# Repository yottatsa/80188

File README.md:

# 80188 single board modular computer

* testing and firmware development: r1
* hardware development: r2
  - [CPU card](https://github.com/yottatsa/80188/blob/main/cpu_card/cpu_card/cpu_card.pdf)
  - [ISP interface](https://github.com/yottatsa/80188/blob/main/cpu_card/isp_interface/isp_interface.pdf)

To emulate

    make run

To program and connect

    make all
    minipro -p SST39SF020A@PLCC32 --write fw/fw.bin
    minipro -p ... --write gal/....pld
    ...
    picocom -q --baud 9600 --imap lfcrlf --omap crlf [serial device]

## Configuration

* 8MHz 8086-compatible CPU
* 128KB low SRAM
* 256KB EEPROM (27C020) or Flash (SST39SF020) with in-system programming and software programming capabilities
* PC/104-compatible with 8-bit ISA bus
  - 80188 Timer A is routed to OSC
* Dual channel 16550-compatible UART
  - FTDI USB-Serial/6-pin connector on port A
  - 5V 9pin connector on port B
* AT-compatible RTC

## Notes

### r1

* minor: SYSBUS socket is too close to the CPU socket and can'tbe used with the wide connector
* minor: 16V8 /OE and GND pin names were swapped
* minor: UART1 labels are wrong
* major: 74x573 OE should be /OE
* major: 16V8 /RESET can't be used as input
* major: PLCC sockets are unreliable
* unknown: 22V10 Verification failed at address 0x16C5: File=0x01, Device=0x00
* feature: added in-system programming
* major: 39x flash doesn't work as /PGM is floating

### r0
* major: PCB socket is unreliable

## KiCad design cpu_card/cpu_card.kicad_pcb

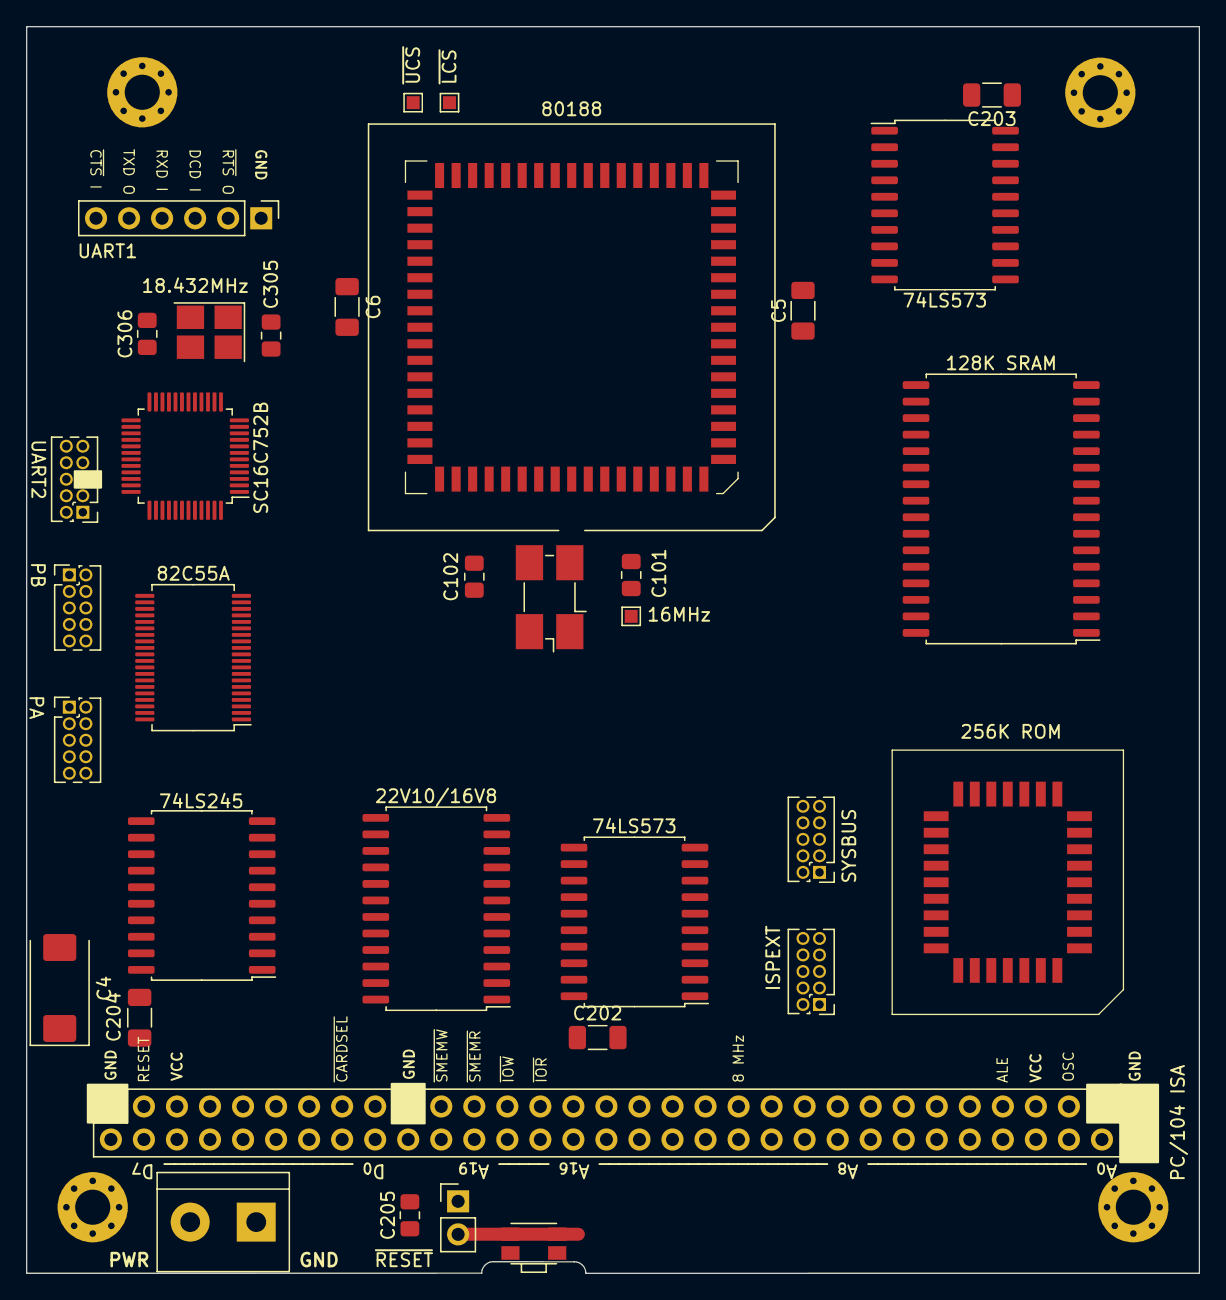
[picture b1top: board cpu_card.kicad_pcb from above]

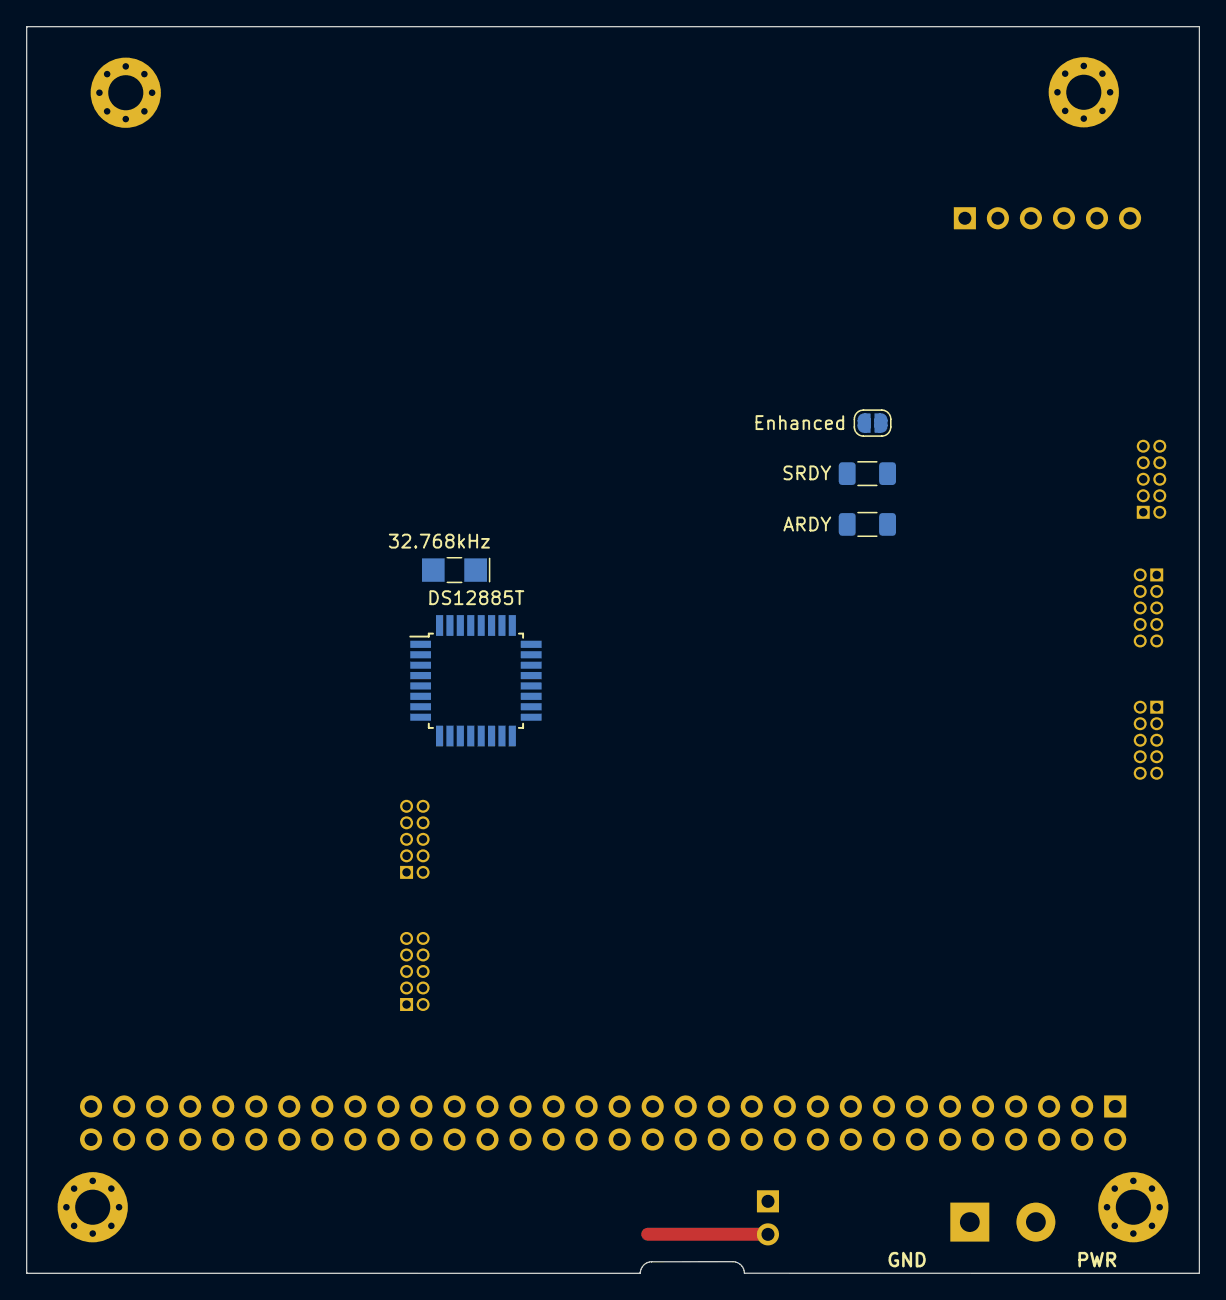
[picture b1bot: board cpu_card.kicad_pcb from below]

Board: 4 copper layers, 90.2 x 95.9 mm, 44 parts (5 on the bottom side), 116 nets.

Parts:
C4: PPWR; CP_EIA-7343-31_Kemet-D
C5, C6, C202, C203, C204: 100n/0.1u PWR; C_1206_3216Metric_Pad1.33x1.80mm_HandSolder
C101, C305: 22p XTAL; C_0805_2012Metric_Pad1.18x1.45mm_HandSolder
C102: 20p XTAL; C_0805_2012Metric_Pad1.18x1.45mm_HandSolder
C205: 20p; C_0805_2012Metric_Pad1.18x1.45mm_HandSolder
C306: 33p XTAL; C_0805_2012Metric_Pad1.18x1.45mm_HandSolder
H1, H2, H3, H4: MountingHole_2.7mm_M2.5_Pad_Via
J101: PC/104 ISA; PinSocket_2x32_P2.54mm_Vertical
J102: SYSBUS; PinHeader_2x05_P1.27mm_Vertical
J103: 80188; PLCC-68_SMD-Socket
J104: 256K ROM; 69802132LF
J201: 22V10/16V8; SOIC-24W_7.5x15.4mm_P1.27mm
J203: ~{RESET}; PinHeader_1x02_P2.54mm_Vertical
J204: ISPEXT; PinHeader_2x05_P1.27mm_Vertical
J301: UART1; PinHeader_1x06_P2.54mm_Vertical
J302: UART2; PinHeader_2x05_P1.27mm_Vertical
J304: PB; PinHeader_2x05_P1.27mm_Vertical
J305: PA; PinHeader_2x05_P1.27mm_Vertical
JP101: Enhanced; SolderJumper-2_P1.3mm_Open_RoundedPad1.0x1.5mm
R2: ARDY; R_1206_3216Metric_Pad1.30x1.75mm_HandSolder
R3: SRDY; R_1206_3216Metric_Pad1.30x1.75mm_HandSolder
S1: PWR; TerminalBlock_bornier-2_P5.08mm
SW201: RESET; SW_SPST_EVQP7A
TP101: XTAL; TestPoint_Pad_1.0x1.0mm
TP103: ~{UCS}; TestPoint_Pad_1.0x1.0mm
TP104: ~{LCS}; TestPoint_Pad_1.0x1.0mm
U101: 128K SRAM; SSOP-32_11.305x20.495mm_P1.27mm
U201, U202: 74LS573; SOIC-20W_7.5x12.8mm_P1.27mm
U203: 74LS245; SOIC-20W_7.5x12.8mm_P1.27mm
U301: SC16C752B; TQFP-48_7x7mm_P0.5mm
U303: DS12885T; TQFP-32_7x7mm_P0.8mm
U304: 82C55A; TSSOP-40_6.1x11mm_P0.5mm
Y1: 16MHz; Crystal_SMD_0603-4Pin_6.0x3.5mm_HandSoldering
Y301: 18.432MHz; Crystal_SMD_3225-4Pin_3.2x2.5mm_HandSoldering
Y302: 32.768kHz; Crystal_SMD_EuroQuartz_EQ161-2Pin_3.2x1.5mm_HandSoldering

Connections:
/X1: C101.2, J103.59 (X1), TP101.1, Y1.1
/X2: C102.1, J103.58 (X2), Y1.3
A0: J101.62, J104.12 (A0), U101.12 (A0), U201.19 (Q0), U301.28 (A0), U304.9 (A0)
A1: J101.60, J104.11 (A1), U101.11 (A1), U201.18 (Q1), U301.27 (A1), U304.8 (A1)
A2: J101.58, J104.10 (A2), U101.10 (A2), U201.17 (Q2), U301.26 (A2)
A3: J101.56, J104.9 (A3), J201.3 (I1), U101.9 (A3), U201.16 (Q3)
A4: J101.54, J104.8 (A4), U101.8 (A4), U201.15 (Q4)
A5: J101.52, J104.7 (A5), U101.7 (A5), U201.14 (Q5)
A6: J101.50, J104.6 (A6), U101.6 (A6), U201.13 (Q6)
A7: J101.48, J104.5 (A7), U101.5 (A7), U201.12 (Q7)
A8: J101.46, J103.16 (A8), J104.27 (A8), U101.27 (A8)
A9: J101.44, J103.14 (A9), U101.26 (A9)
A10: J101.42, J103.12 (A10), J104.23 (A10), U101.23 (A10)
A11: J101.40, J103.10 (A11), J104.25 (A11), U101.25 (A11)
A12: J101.38, J103.7 (A12), J104.4 (A12), U101.4 (A12)
A13: J101.36, J103.5 (A13), J104.28 (A13), U101.28 (A13)
A14: J101.34, J103.3 (A14), J104.29 (A14), U101.3 (A14)
A15: J101.32, J103.1 (A15), J104.3 (A15), U101.31 (A15)
A16: J101.30, J104.2 (A16), U101.2 (A16), U202.16 (Q3)
A17: J101.28, J104.30 (A17), U202.17 (Q2)
A18: J101.26, U202.18 (Q1)
A19: J101.24, U202.19 (Q0)
AD0: J102.1, J103.17 (AD0), J104.13 (D0), U101.13 (Q0), U201.2 (D0), U203.2 (A0), U303.1 (AD0)
AD1: J102.2, J103.15 (AD1), J104.14 (D1), U101.14 (Q1), U201.3 (D1), U203.3 (A1), U303.2 (AD1)
AD2: J102.3, J103.13 (AD2), J104.15 (D2), U101.15 (Q2), U201.4 (D2), U203.4 (A2), U303.3 (AD2)
AD3: J102.4, J103.11 (AD3), J104.17 (D3), U101.17 (Q3), U201.5 (D3), U203.5 (A3), U303.5 (AD3)
AD4: J102.5, J103.8 (AD4), J104.18 (D4), U101.18 (Q4), U201.6 (D4), U203.6 (A4), U303.7 (AD4)
AD5: J102.6, J103.6 (AD5), J104.19 (D5), U101.19 (Q5), U201.7 (D5), U203.7 (A5), U303.8 (AD5)
AD6: J102.7, J103.4 (AD6), J104.20 (D6), U101.20 (Q6), U201.8 (D6), U203.8 (A6), U303.9 (AD6)
AD7: J102.8, J103.2 (AD7), J104.21 (D7), U101.21 (Q7), U201.9 (D7), U203.9 (A7), U303.11 (AD7)
ALE: J101.3, J101.55, J103.61 (ALE/QS0), J201.23 (O0/LR), U201.1 (OE), U201.11 (Load), U202.1 (OE), U202.11 (Load), U301.36 (RESET), U303.14 (AS), U304.35 (RESET)
BCLK: J101.39, J103.56 (CLKOUT)
DB0: J101.18, U203.18 (B0), U301.44 (D0), U304.34 (D0)
DB1: J101.16, U203.17 (B1), U301.45 (D1), U304.33 (D1)
DB2: J101.14, U203.16 (B2), U301.46 (D2), U304.32 (D2)
DB3: J101.12, U203.15 (B3), U301.47 (D3), U304.31 (D3)
DB4: J101.10, U203.14 (B4), U301.48 (D4), U304.30 (D4)
DB5: J101.8, U203.13 (B5), U301.1 (D5), U304.29 (D5)
DB6: J101.6, U203.12 (B6), U301.2 (D6), U304.28 (D6)
DB7: J101.4, U203.11 (B7), U301.3 (D7), U304.27 (D7)
DCD: J201.10 (I8), J301.3
DRQ0: J101.35, J103.18 (DRQ0)
DRQ1: J101.11, J103.19 (DRQ1)
DT/~R: J103.40 (DT/~R), U203.1 (A->B)
GND: C4.2, C5.2, C6.2, C101.1, C102.2, C202.2, C203.2, C204.2, C205.2, C305.1, C306.2, H1.1, H2.1, H3.1, H4.1, J101.1, J101.19, J101.61, J101.63, J101.64, J102.9, J103.26 (VSS), J103.50 (HOLD), J103.60 (VSS), J104.16 (GND), J201.12 (GND), J203.1, J301.1, J302.5, J304.9, J305.9, S1.1, SW201.2, U101.16 (GND), U201.10 (GND), U202.10 (GND), U203.10 (GND), U301.17 (GND), U303.12 (GND), U303.17 (GND), U303.29 (MOT), U304.7 (GND)
INT0: J103.45 (INT0), U301.30 (INTA)
INT1: J101.7, J103.44 (INT1/~SELECT)
INT2: J103.42 (INT2/~INTA0), U301.29 (INTB)
INT3: J101.49, J103.41 (INT3/~INTA1/IRQ)
M/~IO: J201.6 (I4), U202.15 (Q4)
unnamed: C305.2, U301.13 (XTAL1), Y301.1
unnamed: C306.1, U301.14 (XTAL2), Y301.3
unnamed: J103.47 (~TEST), JP101.2 (B)
unnamed: J103.49 (SRDY), R3.2
unnamed: J103.55 (ARDY), R2.2
unnamed: J304.1, U304.18 (PB0)
unnamed: J304.2, U304.19 (PB1)
unnamed: J304.3, U304.20 (PB2)
unnamed: J304.4, U304.21 (PB3)
unnamed: J304.5, U304.22 (PB4)
unnamed: J304.6, U304.23 (PB5)
unnamed: J304.7, U304.24 (PB6)
unnamed: J304.8, U304.25 (PB7)
unnamed: J305.1, U304.4 (PA0)
unnamed: J305.2, U304.3 (PA1)
unnamed: J305.3, U304.2 (PA2)
unnamed: J305.4, U304.1 (PA3)
unnamed: J305.5, U304.40 (PA4)
unnamed: J305.6, U304.39 (PA5)
unnamed: J305.7, U304.38 (PA6)
unnamed: J305.8, U304.37 (PA7)
unnamed: U303.30 (X1), Y302.1
unnamed: U303.31 (X2), Y302.2
RESOUT: J103.57 (RESET), J201.2 (I0), JP101.1 (A)
ROM.A9: J104.26 (A9), J204.1
ROM.~OE: J104.24 (~OE), J204.3
ROM.~WE: J104.31 (~PGM), J204.2
TMR_OUT_0: J101.59, J103.22 (TMR_OUT_0)
UART1.IN: J301.4, U301.5 (RXA)
UART1.OUT: J301.5, U301.7 (TXA)
UART1.~CTS: J301.6, U301.38 (~CTSA)
UART1.~RTS: J301.2, U301.33 (~RTSA)
UART2.RX: J302.2, U301.4 (RXB)
UART2.TX: J302.3, U301.8 (TXB)
UART2.~CD: J302.1, U301.16 (~CDB)
UART2.~CTS: J302.8, U301.23 (~CTSB)
UART2.~DSR: J302.6, U301.20 (~DSRB)
UART2.~DTR: J302.4, U301.35 (~DTRB)
UART2.~RI: J302.9, U301.21 (~RIB)
UART2.~RTS: J302.7, U301.22 (~RTSB)
VCC: C4.1, C5.1, C6.1, C202.1, C203.1, C204.1, J101.5, J101.57, J103.9 (VCC), J103.43 (VCC), J104.32 (VCC), J201.24 (VCC), R2.1, R3.1, S1.2, U101.30 (CS2), U101.32 (VCC), U201.20 (VCC), U202.20 (VCC), U203.20 (VCC), U301.42 (VCC), U303.28 (VCC), U304.26 (VCC)
XA16: J103.68 (A16/S3), U202.5 (D3)
XA17: J103.67 (A17/S4), U202.4 (D2)
XA18: J103.66 (A18/S5), U202.3 (D1)
XA19: J103.65 (A19/S6), U202.2 (D0)
~BEN: J201.16 (A1/O2), U203.19 (CE)
~CARDSLCTD: J101.15, J201.8 (I6)
~CS_RTC: J103.27 (~PCS1), U303.13 (~CS)
~CS_S1: J201.22 (O1/A0), U301.10 (~CSA)
~CS_S2: J201.14 (LR/O4), U301.11 (~CSB)
~CS_S: J103.25 (~PCS0), J201.7 (I5)
~DEN: J103.39 (~DEN), J201.9 (I7)
~IOR: J101.27, J201.21 (O2/A1), U301.19 (~IOR), U304.5 (~RD)
~IOW: J101.25, J201.20 (O3/A2), U301.15 (~IOW), U304.36 (~WR)
~LCS: J103.33 (~LCS), J204.10, TP104.1, U101.22 (~CS1)
~PCS3: J101.37, J103.29 (~PCS3)
~PCS4: J101.33, J103.30 (~PCS4)
~PCS5: J101.51, J103.31 (~PCS5/A1)
~PCS6: J101.29, J103.32 (~PCS6/A2)
~RD: J103.62 (~RD/~QSMD), J201.5 (I3), J204.5, U101.24 (~OE), U303.18 (DS)
~RESET: C205.1, J103.24 (~RES), J201.17 (A2/O1), J203.2, J204.9, SW201.1, U303.19 (~RESET)
~S2: J103.54 (~S2), U202.6 (D4)
~SMEMR: J101.23, J201.19 (O4/NC)
~SMEMW: J101.21, J201.18 (NC/O0)
~UCS: J103.34 (~UCS), J104.22 (~CE), J204.8, TP103.1
~WR: J103.63 (~WR/QS1), J201.4 (I2), J204.4, U101.29 (~WE), U303.16 (R/*W)

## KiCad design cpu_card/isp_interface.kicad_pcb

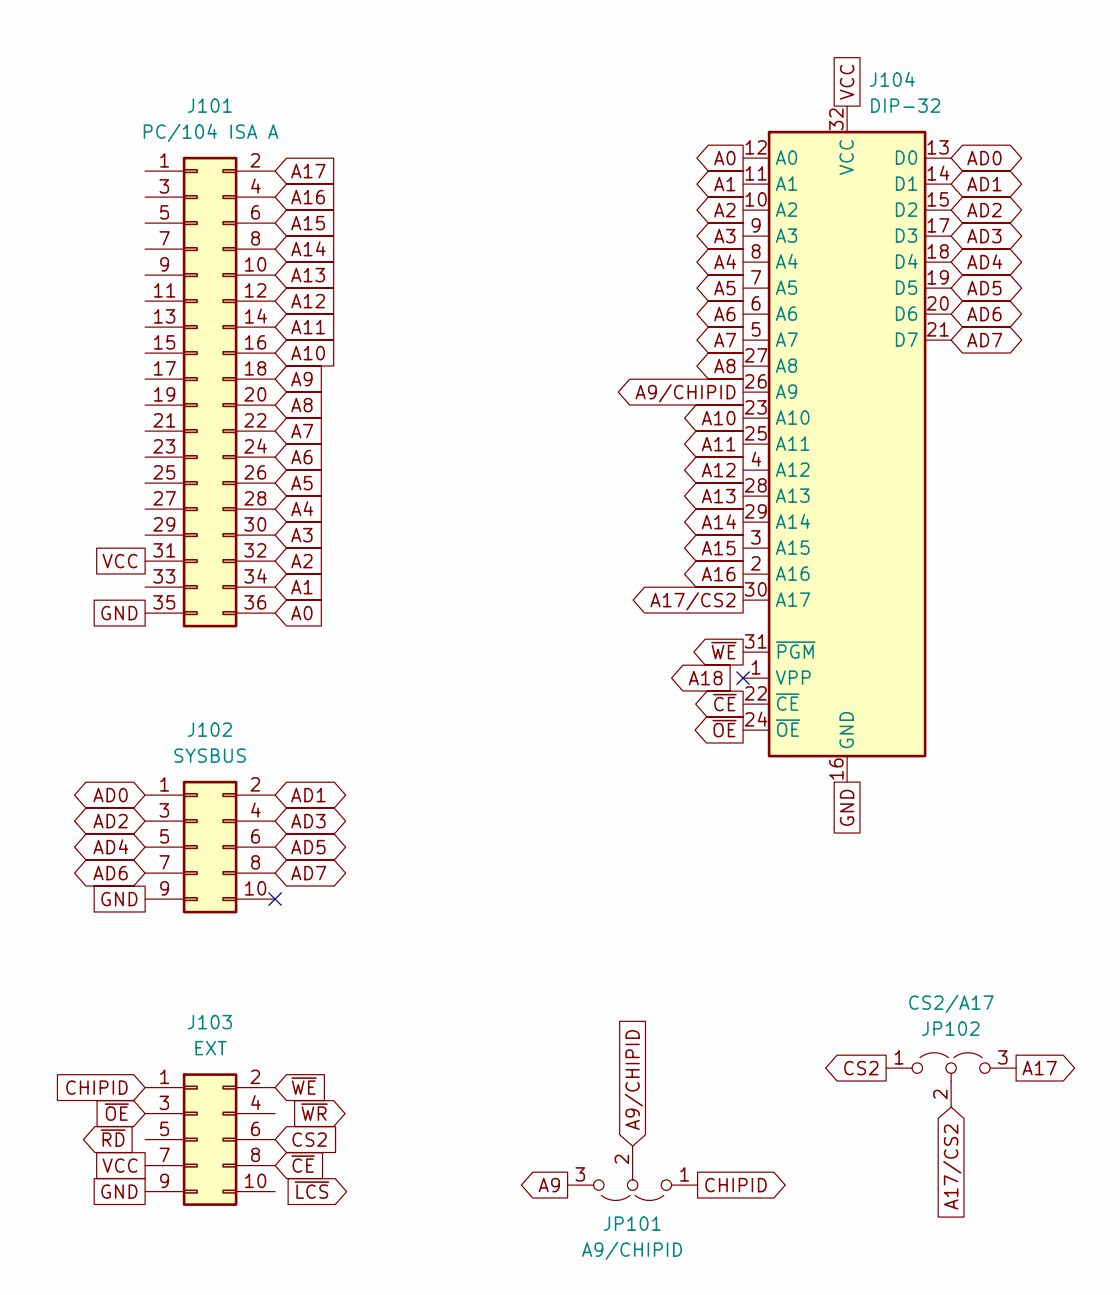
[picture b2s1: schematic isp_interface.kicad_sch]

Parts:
J101: PC/104 ISA A; PinSocket_2x18_P2.54mm_Vertical
J102: SYSBUS; PinHeader_2x05_P1.27mm_Vertical
J103: EXT; PinHeader_2x05_P1.27mm_Vertical
J104: DIP-32; DIP-32_W15.24mm_LongPads; Manufacturer_Part_Number SST39SF020A-70-4C-NHE; Mouser Part Number 804-39SF020A7CNHE
JP101: A9/CHIPID; PinHeader_1x03_P2.54mm_Vertical
JP102: CS2/A17; PinHeader_1x03_P2.54mm_Vertical

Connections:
A0: J101.36, J104.12 (A0)
A1: J101.34, J104.11 (A1)
A2: J101.32, J104.10 (A2)
A3: J101.30, J104.9 (A3)
A4: J101.28, J104.8 (A4)
A5: J101.26, J104.7 (A5)
A6: J101.24, J104.6 (A6)
A7: J101.22, J104.5 (A7)
A8: J101.20, J104.27 (A8)
A9: J101.18, JP101.3 (B)
A9/CHIPID: J104.26 (A9), JP101.2 (C)
A10: J101.16, J104.23 (A10)
A11: J101.14, J104.25 (A11)
A12: J101.12, J104.4 (A12)
A13: J101.10, J104.28 (A13)
A14: J101.8, J104.29 (A14)
A15: J101.6, J104.3 (A15)
A16: J101.4, J104.2 (A16)
A17: J101.2, JP102.3 (B)
A17/CS2: J104.30 (A17), JP102.2 (C)
AD0: J102.1, J104.13 (D0)
AD1: J102.2, J104.14 (D1)
AD2: J102.3, J104.15 (D2)
AD3: J102.4, J104.17 (D3)
AD4: J102.5, J104.18 (D4)
AD5: J102.6, J104.19 (D5)
AD6: J102.7, J104.20 (D6)
AD7: J102.8, J104.21 (D7)
CHIPID: J103.1, JP101.1 (A)
CS2: J103.6, JP102.1 (A)
GND: J101.35, J102.9, J103.9, J104.16 (GND)
VCC: J101.31, J103.7, J104.32 (VCC)
~CE: J103.8, J104.22 (~CE)
~OE: J103.3, J104.24 (~OE)
~WE: J103.2, J104.31 (~PGM)

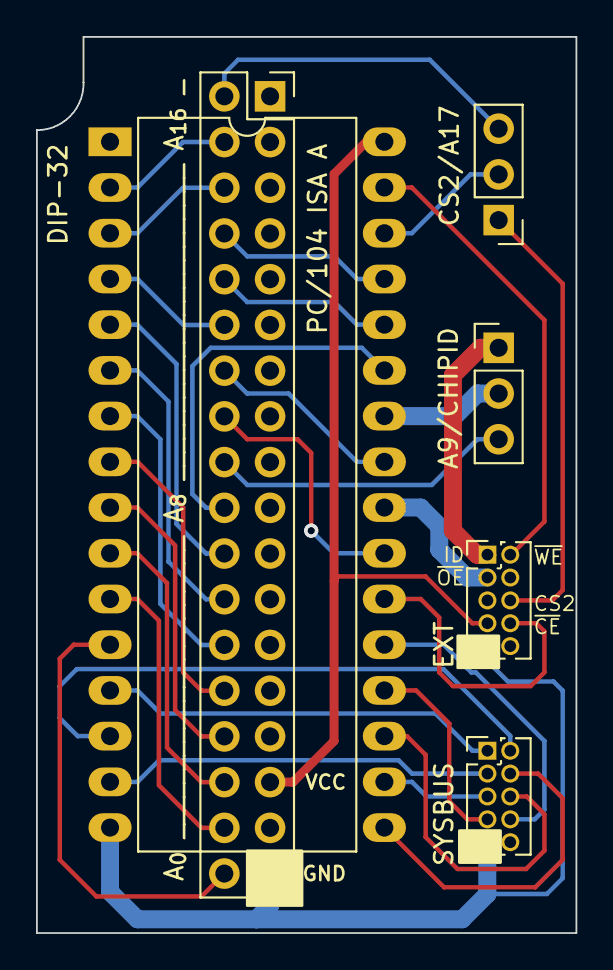
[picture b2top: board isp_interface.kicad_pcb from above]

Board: 2 copper layers, 30.0 x 49.8 mm, 6 parts (0 on the bottom side), 35 nets.

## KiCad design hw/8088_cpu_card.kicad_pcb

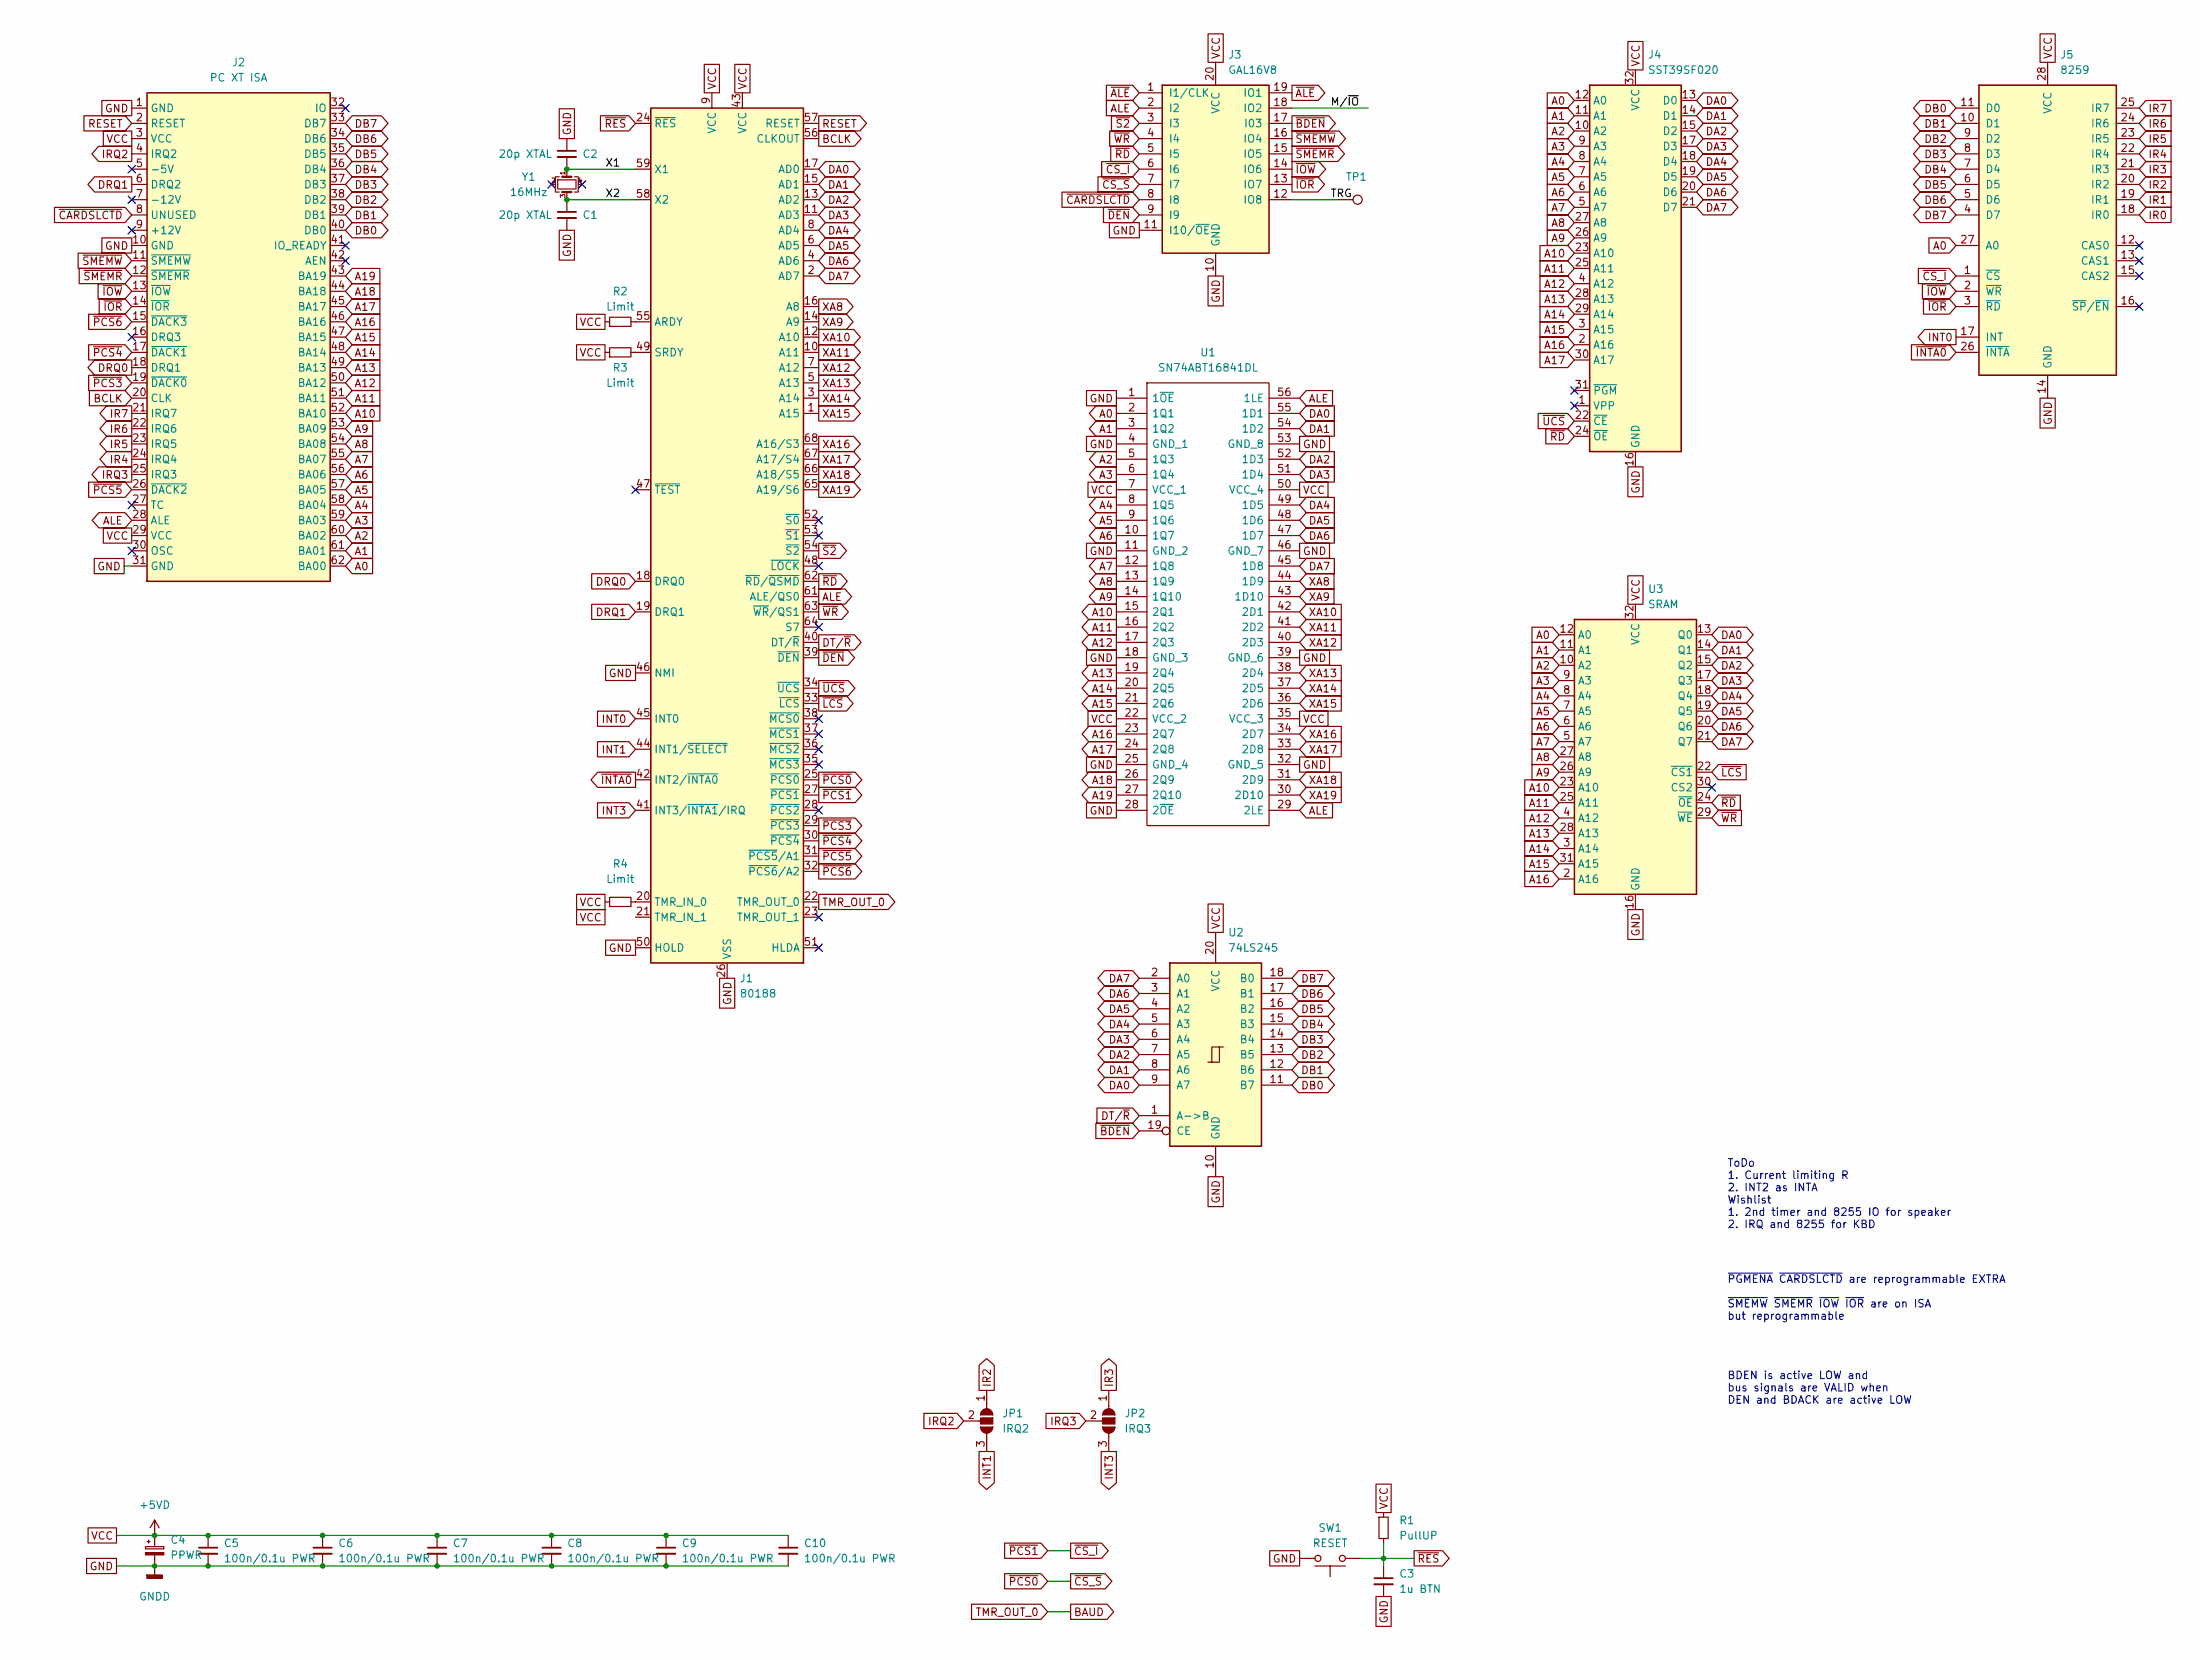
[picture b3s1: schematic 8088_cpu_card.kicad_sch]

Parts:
C1, C2: 20p XTAL; C_0402_1005Metric_Pad0.74x0.62mm_HandSolder; Manufacturer_Part_Number GJM1555C1H200FB01D
C3: 1u BTN; C_0805_2012Metric_Pad1.18x1.45mm_HandSolder; Mouser Part Number 80-C0805C105M3RECLR
C4: PPWR; CP_EIA-7343-31_Kemet-D; Mouser Part Number 667-EEF-CS1D100R
C5, C6, C7, C8, C9, C10: 100n/0.1u PWR; C_1206_3216Metric_Pad1.33x1.80mm_HandSolder; Mouser Part Number 80-C1206X104G4HACTU
J1: 80188; PGA68-N; Manufacturer_Part_Number 8468-11B1-RK-TP; Mouser Part Number 517-8468-11B1-RK-TP
J2: PC XT ISA; ISA-X
J3: GAL16V8; DIP-20_W7.62mm; Manufacturer_Part_Number ATF16V8CZ-15PU; Mouser Part Number 556-AF16V8CZ15PU
J4: SST39SF020; PLCC-32_THT-Socket; Manufacturer_Part_Number SST39SF020A-70-4C-NHE; Mouser Part Number 804-39SF020A7CNHE
J5: 8259; PLCC-28_THT-Socket
JP1: IRQ2; SolderJumper-3_P1.3mm_Open_RoundedPad1.0x1.5mm
JP2: IRQ3; SolderJumper-3_P1.3mm_Open_RoundedPad1.0x1.5mm
R1: PullUP; R_1206_3216Metric_Pad1.30x1.75mm_HandSolder; Mouser Part Number 71-RCC120620K0FKEA
R2, R3, R4: Limit; R_1206_3216Metric_Pad1.30x1.75mm_HandSolder; Mouser Part Number 71-RCC120620K0FKEA
SW1: RESET; SW_SPST_EVQP7A; Manufacturer_Part_Number EVQ-P7J01P; Mouser Part Number 667-EVQP7J01P
TP1: (no value)
U1: SN74ABT16841DL; SOP64P1035X279-56N; Mouser Part Number 595-74ACT16841DL
U2: 74LS245; SOIC-20W_7.5x12.8mm_P1.27mm; Manufacturer_Part_Number SN74LS245DW; Mouser Part Number 595-SN74LS245DW
U3: SRAM; SSOP-32_11.305x20.495mm_P1.27mm; Manufacturer_Part_Number IS62C1024AL-35QLI
Y1: 16MHz; Crystal_SMD_0603-4Pin_6.0x3.5mm_HandSoldering

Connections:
/M/~IO: J3.18 (IO2)
/TRG: J3.12 (IO8), TP1.1
/X1: C2.2, J1.59 (X1), Y1.1
/X2: C1.1, J1.58 (X2), Y1.3
A0: J2.62 (BA00), J4.12 (A0), J5.27 (A0), U1.2 (1Q1), U3.12 (A0)
A1: J2.61 (BA01), J4.11 (A1), U1.3 (1Q2), U3.11 (A1)
A2: J2.60 (BA02), J4.10 (A2), U1.5 (1Q3), U3.10 (A2)
A3: J2.59 (BA03), J4.9 (A3), U1.6 (1Q4), U3.9 (A3)
A4: J2.58 (BA04), J4.8 (A4), U1.8 (1Q5), U3.8 (A4)
A5: J2.57 (BA05), J4.7 (A5), U1.9 (1Q6), U3.7 (A5)
A6: J2.56 (BA06), J4.6 (A6), U1.10 (1Q7), U3.6 (A6)
A7: J2.55 (BA07), J4.5 (A7), U1.12 (1Q8), U3.5 (A7)
A8: J2.54 (BA08), J4.27 (A8), U1.13 (1Q9), U3.27 (A8)
A9: J2.53 (BA09), J4.26 (A9), U1.14 (1Q10), U3.26 (A9)
A10: J2.52 (BA10), J4.23 (A10), U1.15 (2Q1), U3.23 (A10)
A11: J2.51 (BA11), J4.25 (A11), U1.16 (2Q2), U3.25 (A11)
A12: J2.50 (BA12), J4.4 (A12), U1.17 (2Q3), U3.4 (A12)
A13: J2.49 (BA13), J4.28 (A13), U1.19 (2Q4), U3.28 (A13)
A14: J2.48 (BA14), J4.29 (A14), U1.20 (2Q5), U3.3 (A14)
A15: J2.47 (BA15), J4.3 (A15), U1.21 (2Q6), U3.31 (A15)
A16: J2.46 (BA16), J4.2 (A16), U1.23 (2Q7), U3.2 (A16)
A17: J2.45 (BA17), J4.30 (A17), U1.24 (2Q8)
A18: J2.44 (BA18), U1.26 (2Q9)
A19: J2.43 (BA19), U1.27 (2Q10)
ALE: J1.61 (ALE/QS0), J2.28 (ALE), J3.2 (I2), U1.29 (2LE), U1.56 (1LE)
BAUD: J1.22 (TMR_OUT_0)
BCLK: J1.56 (CLKOUT), J2.20 (CLK)
DA0: J1.17 (AD0), J4.13 (D0), U1.55 (1D1), U2.9 (A7), U3.13 (Q0)
DA1: J1.15 (AD1), J4.14 (D1), U1.54 (1D2), U2.8 (A6), U3.14 (Q1)
DA2: J1.13 (AD2), J4.15 (D2), U1.52 (1D3), U2.7 (A5), U3.15 (Q2)
DA3: J1.11 (AD3), J4.17 (D3), U1.51 (1D4), U2.6 (A4), U3.17 (Q3)
DA4: J1.8 (AD4), J4.18 (D4), U1.49 (1D5), U2.5 (A3), U3.18 (Q4)
DA5: J1.6 (AD5), J4.19 (D5), U1.48 (1D6), U2.4 (A2), U3.19 (Q5)
DA6: J1.4 (AD6), J4.20 (D6), U1.47 (1D7), U2.3 (A1), U3.20 (Q6)
DA7: J1.2 (AD7), J4.21 (D7), U1.45 (1D8), U2.2 (A0), U3.21 (Q7)
DB0: J2.40 (DB0), J5.11 (D0), U2.11 (B7)
DB1: J2.39 (DB1), J5.10 (D1), U2.12 (B6)
DB2: J2.38 (DB2), J5.9 (D2), U2.13 (B5)
DB3: J2.37 (DB3), J5.8 (D3), U2.14 (B4)
DB4: J2.36 (DB4), J5.7 (D4), U2.15 (B3)
DB5: J2.35 (DB5), J5.6 (D5), U2.16 (B2)
DB6: J2.34 (DB6), J5.5 (D6), U2.17 (B1)
DB7: J2.33 (DB7), J5.4 (D7), U2.18 (B0)
DRQ0: J1.18 (DRQ0), J2.18 (DRQ1)
DRQ1: J1.19 (DRQ1), J2.6 (DRQ2)
DT/~R: J1.40 (DT/~R), U2.1 (A->B)
GND: C1.2, C2.1, C3.2, C4.2, C5.2, C6.2, C7.2, C8.2, C9.2, C10.2, J1.26 (VSS), J1.46 (NMI), J1.50 (HOLD), J1.60 (VSS), J2.1 (GND), J2.10 (GND), J2.31 (GND), J3.10 (GND), J3.11 (I10/~OE), J4.16 (GND), J5.14 (GND), SW1.2, U1.1 (1~OE), U1.4 (GND_1), U1.11 (GND_2), U1.18 (GND_3), U1.25 (GND_4), U1.28 (2~OE), U1.32 (GND_5), U1.39 (GND_6), U1.46 (GND_7), U1.53 (GND_8), U2.10 (GND), U3.16 (GND)
INT0: J1.45 (INT0), J5.17 (INT)
INT1: J1.44 (INT1/~SELECT), JP1.3 (B)
INT3: J1.41 (INT3/~INTA1/IRQ), JP2.3 (B)
IR0: J5.18 (IR0)
IR1: J5.19 (IR1)
IR2: J5.20 (IR2), JP1.1 (A)
IR3: J5.21 (IR3), JP2.1 (A)
IR4: J2.24 (IRQ4), J5.22 (IR4)
IR5: J2.23 (IRQ5), J5.23 (IR5)
IR6: J2.22 (IRQ6), J5.24 (IR6)
IR7: J2.21 (IRQ7), J5.25 (IR7)
IRQ2: J2.4 (IRQ2), JP1.2 (C)
IRQ3: J2.25 (IRQ3), JP2.2 (C)
unnamed: J1.20 (TMR_IN_0), R4.2
unnamed: J1.49 (SRDY), R3.2
unnamed: J1.55 (ARDY), R2.2
RESET: J1.57 (RESET), J2.2 (RESET)
VCC: C4.1, C5.1, C6.1, C7.1, C8.1, C9.1, C10.1, J1.9 (VCC), J1.43 (VCC), J2.3 (VCC), J2.29 (VCC), J3.20 (VCC), J4.32 (VCC), J5.28 (VCC), R1.1, R2.1, R3.1, R4.1, U1.7 (VCC_1), U1.22 (VCC_2), U1.35 (VCC_3), U1.50 (VCC_4), U2.20 (VCC), U3.32 (VCC)
XA8: J1.16 (A8), U1.44 (1D9)
XA9: J1.14 (A9), U1.43 (1D10)
XA10: J1.12 (A10), U1.42 (2D1)
XA11: J1.10 (A11), U1.41 (2D2)
XA12: J1.7 (A12), U1.40 (2D3)
XA13: J1.5 (A13), U1.38 (2D4)
XA14: J1.3 (A14), U1.37 (2D5)
XA15: J1.1 (A15), U1.36 (2D6)
XA16: J1.68 (A16/S3), U1.34 (2D7)
XA17: J1.67 (A17/S4), U1.33 (2D8)
XA18: J1.66 (A18/S5), U1.31 (2D9)
XA19: J1.65 (A19/S6), U1.30 (2D10)
~ALE: J3.1 (I1/CLK), J3.19 (IO1)
~BDEN: J3.17 (I03), U2.19 (CE)
~CARDSLCTD: J2.8 (UNUSED), J3.8 (I8)
~CS_I: J1.27 (~PCS1), J3.6 (I6), J5.1 (~CS)
~CS_S: J1.25 (~PCS0), J3.7 (I7)
~DEN: J1.39 (~DEN), J3.9 (I9)
~INTA0: J1.42 (INT2/~INTA0), J5.26 (~INTA)
~IOR: J2.14 (~IOR), J3.13 (IO7), J5.3 (~RD)
~IOW: J2.13 (~IOW), J3.14 (IO6), J5.2 (~WR)
~LCS: J1.33 (~LCS), U3.22 (~CS1)
~PCS3: J1.29 (~PCS3), J2.19 (~DACK0)
~PCS4: J1.30 (~PCS4), J2.17 (~DACK1)
~PCS5: J1.31 (~PCS5/A1), J2.26 (~DACK2)
~PCS6: J1.32 (~PCS6/A2), J2.15 (~DACK3)
~RD: J1.62 (~RD/~QSMD), J3.5 (I5), J4.24 (~OE), U3.24 (~OE)
~RES: C3.1, J1.24 (~RES), R1.2, SW1.1
~S2: J1.54 (~S2), J3.3 (I3)
~SMEMR: J2.12 (~SMEMR), J3.15 (IO5)
~SMEMW: J2.11 (~SMEMW), J3.16 (IO4)
~UCS: J1.34 (~UCS), J4.22 (~CE)
~WR: J1.63 (~WR/QS1), J3.4 (I4), U3.29 (~WE)

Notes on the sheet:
~{PGMENA} ~{CARDSLCTD} are reprogrammable EXTRA ~{SMEMW} ~{SMEMR} ~{IOW} ~{IOR} are on ISA but reprogrammable
BDEN is active LOW and bus signals are VALID when DEN and BDACK are active LOW
ToDo 1. Current limiting R 2. INT2 as INTA Wishlist 1. 2nd timer and 8255 IO for speaker 2. IRQ and 8255 for KBD

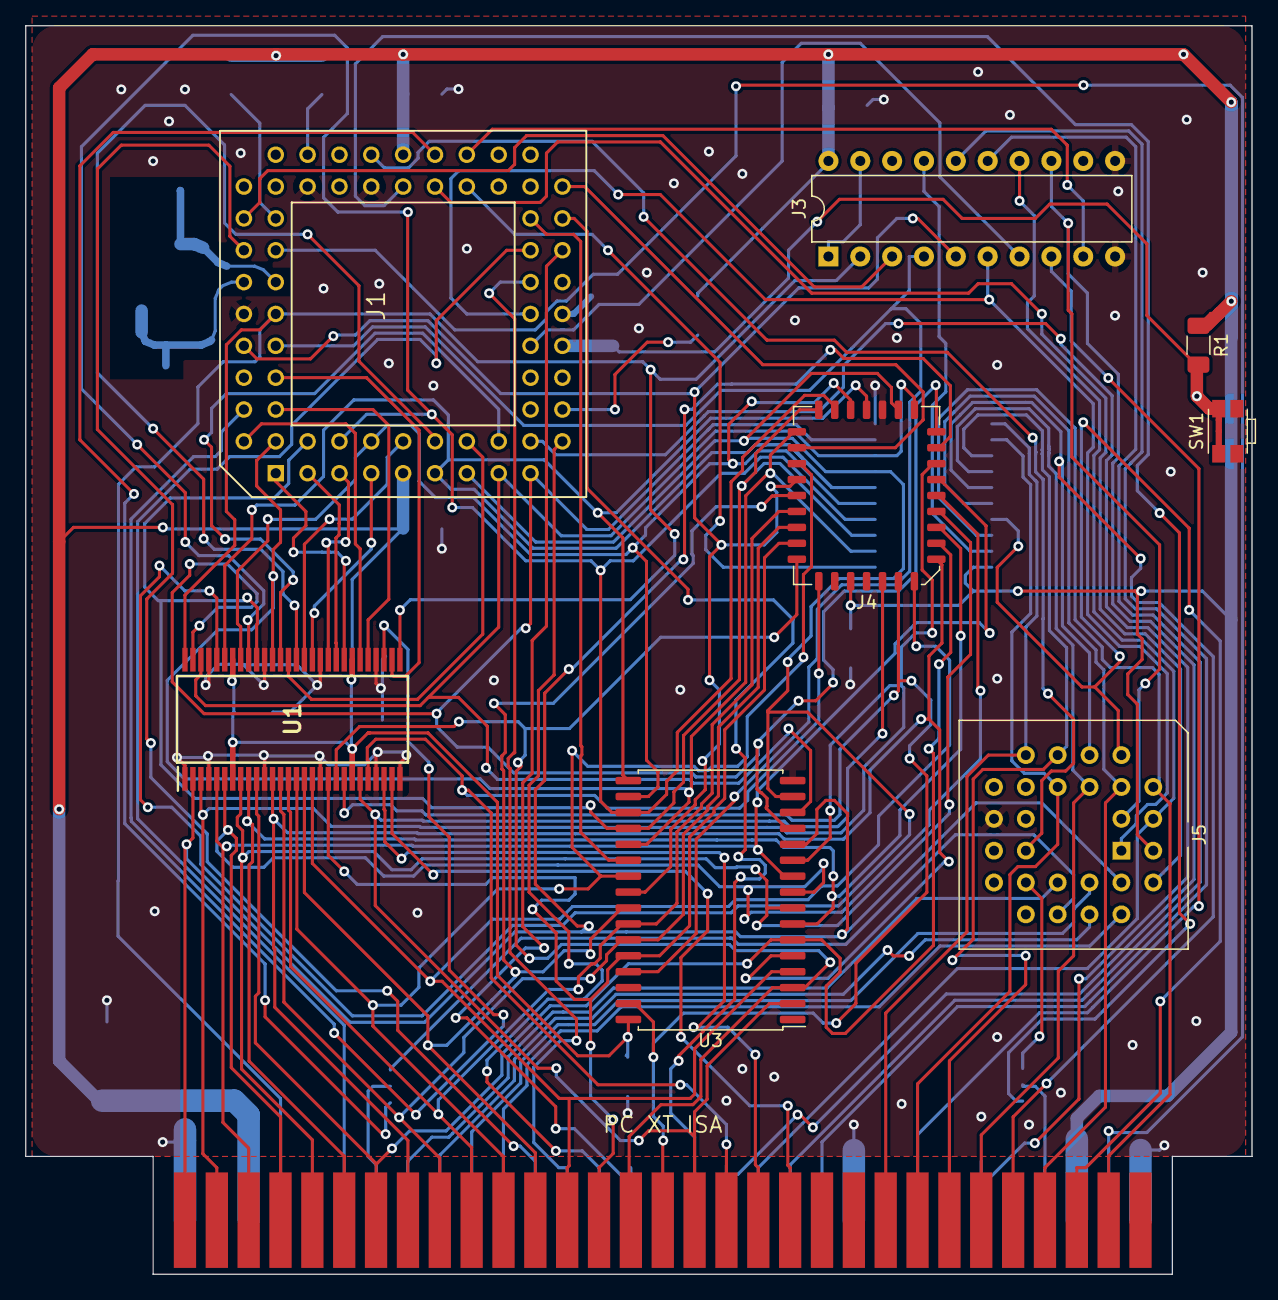
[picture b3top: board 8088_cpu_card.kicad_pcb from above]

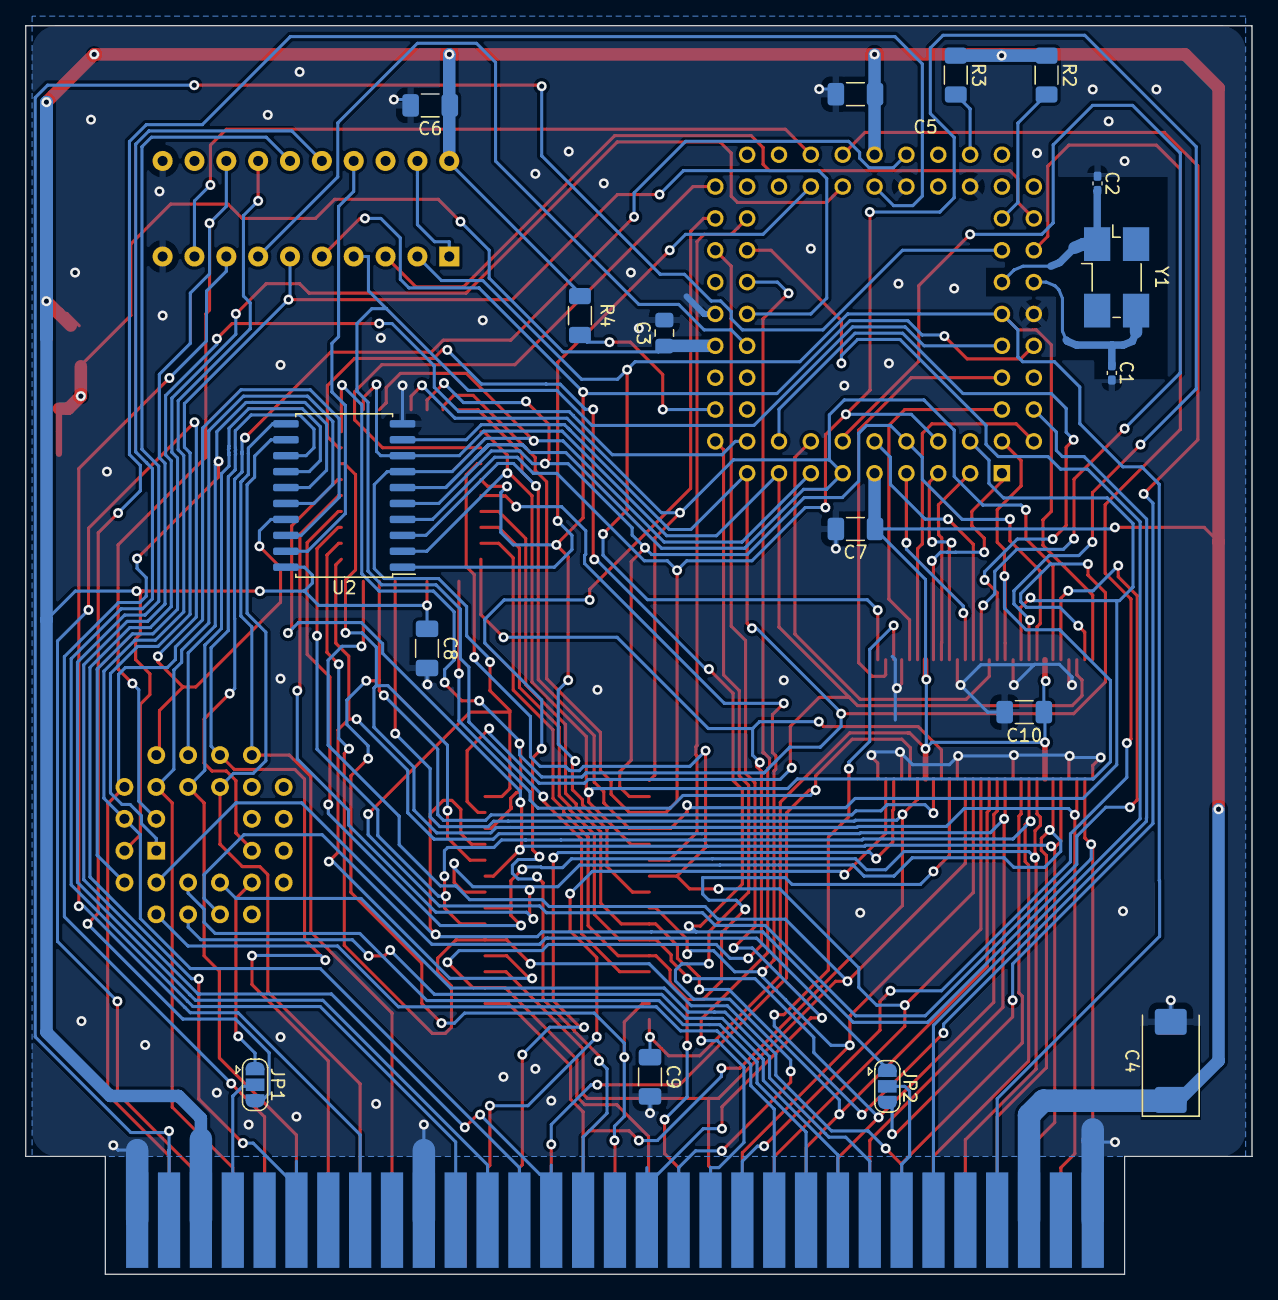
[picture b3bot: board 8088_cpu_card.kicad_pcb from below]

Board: 2 copper layers, 97.8 x 99.6 mm, 26 parts (17 on the bottom side), 93 nets.
